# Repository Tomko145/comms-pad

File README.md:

# Hackpad submission
## Graphics
### Layout schematic

### Fusion360 case render with pcb inside

### Kicad PCB design

### Kicad Electrical schematic

My Hackpad for comms (comunication) with a rotary encoder for volume, 12 keys and a screen (It took me long because im sick and i cant think ) 

Details TBD
# Firmware
## Prototype firmware
For now written in Python with QMK for basic HID functionality. It does not include any screen functionality.
## Final firmware
The firmware is going to be written in rust (to maximise resource control allowing for more complexity) and will run on a p2p infrastructure with a daemon on the target pc allowing for more advanced macros. The complexity is too big to write without the microcontroller available

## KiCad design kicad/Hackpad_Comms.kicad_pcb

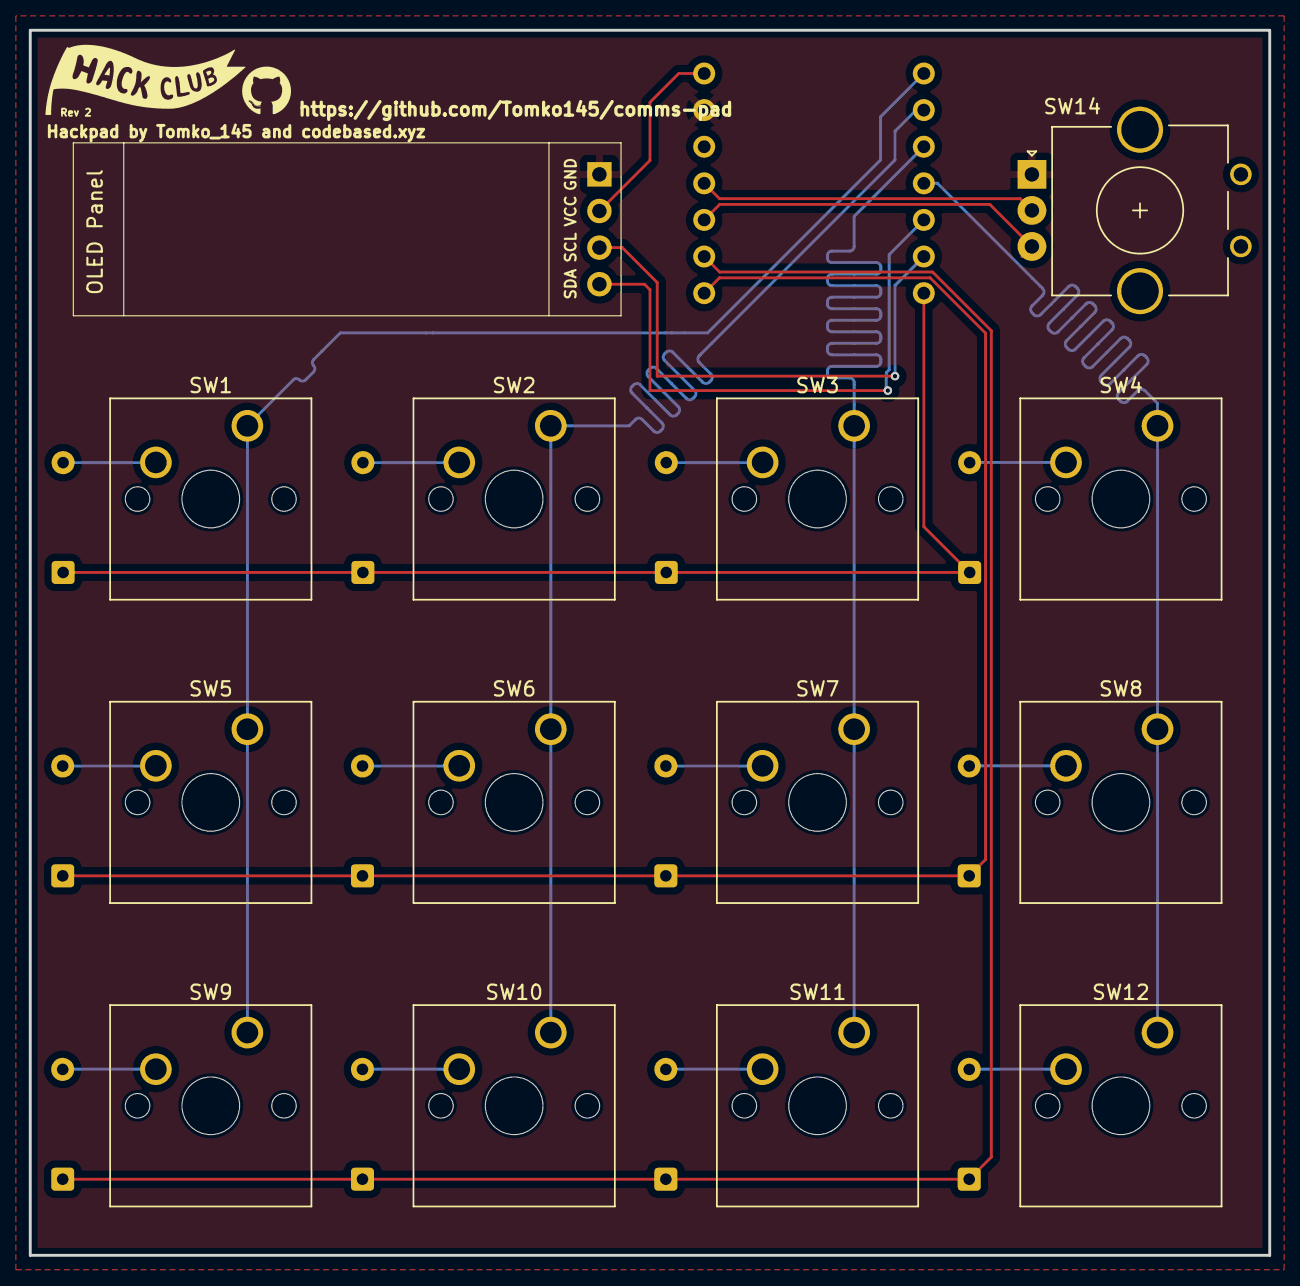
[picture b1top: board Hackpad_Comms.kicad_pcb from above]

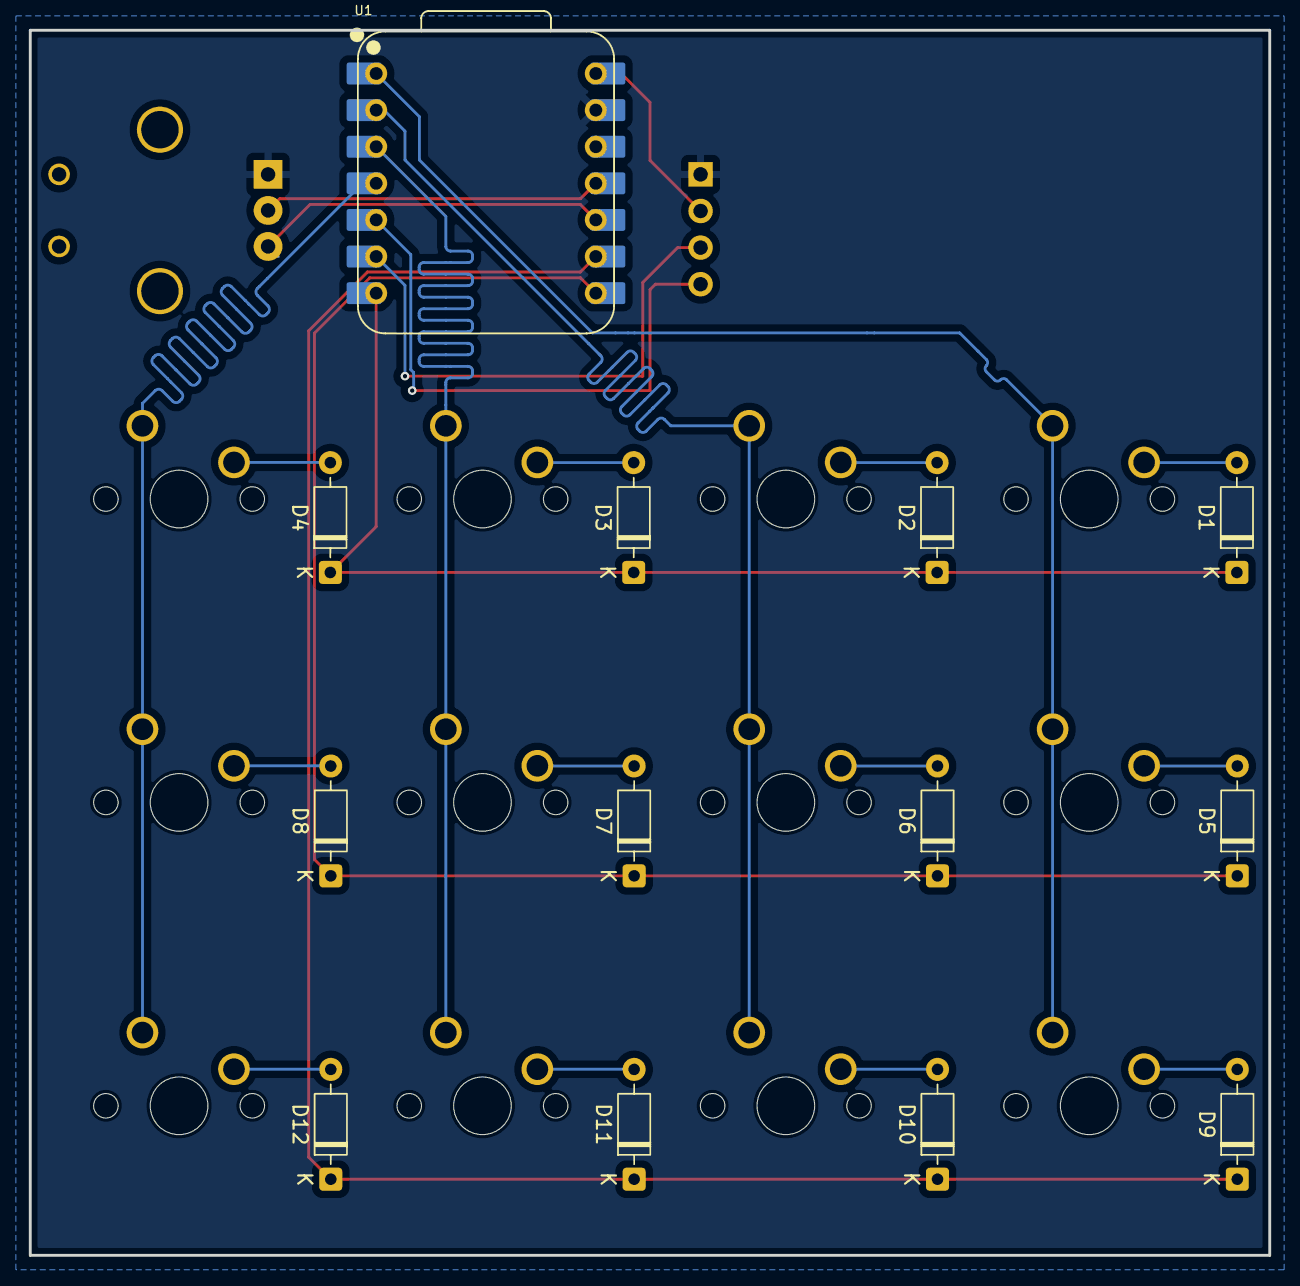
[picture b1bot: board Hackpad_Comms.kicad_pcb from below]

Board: 2 copper layers, 86.0 x 85.0 mm, 27 parts (13 on the bottom side), 23 nets.

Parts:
D1, D2, D3, D4, D5, D6, D7, D8, D9, D10, D11, D12: 1N4148; D_DO-35_SOD27_P7.62mm_Horizontal
OLED: SSD1306-0.91-OLED-4pin-128x32
SW1, SW2, SW3, SW4, SW5, SW6, SW7, SW8, SW9, SW10, SW11, SW12: SW_Push; SW_Cherry_MX_1.00u_PCB
SW14: RotaryEncoder; RotaryEncoder_Alps_EC11E_Vertical_H20mm_CircularMountingHol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
U1: XIAO-RP2040-DIP

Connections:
GND: OLED.1, SW14.A, U1.13 (GND)
unnamed: D1.2 (A), SW1.2
unnamed: D1.1 (K), D2.1 (K), D3.1 (K), D4.1 (K), U1.7 (GPIO0/TX)
unnamed: D2.2 (A), SW2.2
unnamed: D3.2 (A), SW3.2
unnamed: D4.2 (A), SW4.2
unnamed: D5.2 (A), SW5.2
unnamed: D5.1 (K), D6.1 (K), D7.1 (K), D8.1 (K), U1.8 (GPIO1/RX)
unnamed: D6.2 (A), SW6.2
unnamed: D7.2 (A), SW7.2
unnamed: D8.2 (A), SW8.2
unnamed: D9.2 (A), SW9.2
unnamed: D10.2 (A), SW10.2
unnamed: D9.1 (K), D10.1 (K), D11.1 (K), D12.1 (K), U1.9 (GPIO2/SCK)
unnamed: D11.2 (A), SW11.2
unnamed: D12.2 (A), SW12.2
unnamed: OLED.4, U1.5 (GPIO6/SDA)
unnamed: OLED.3, U1.6 (GPIO7/SCL)
unnamed: SW1.1, SW5.1, SW9.1, U1.1 (GPIO26/ADC0/A0)
unnamed: SW2.1, SW6.1, SW10.1, U1.2 (GPIO27/ADC1/A1)
unnamed: SW3.1, SW7.1, SW11.1, U1.3 (GPIO28/ADC2/A2)
unnamed: SW4.1, SW8.1, SW12.1, U1.4 (GPIO29/ADC3/A3)
VCC: OLED.2, U1.14 (VBUS)

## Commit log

2025-12-06 Initial version control (rebase)
2025-12-06 affinity project and more precise vector graphics
2025-12-10 PCB Rev2; Add more images; Basic HID firmware prototype
